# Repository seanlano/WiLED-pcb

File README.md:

# WiLED: PCB files

Circuit schematic and PCB for the WiLED main board, based on the ESP32 (ESP-WROOM-32) module. New version 3.0 of the board is an upgrade from the ESP8266-based version 1.0, but features improved layout and on-board LED driver components.

# Licence

All hardware schematics and design files are released under the CERN Open Hardware Licence v1.2. Please see [LICENCE](LICENCE) for details.

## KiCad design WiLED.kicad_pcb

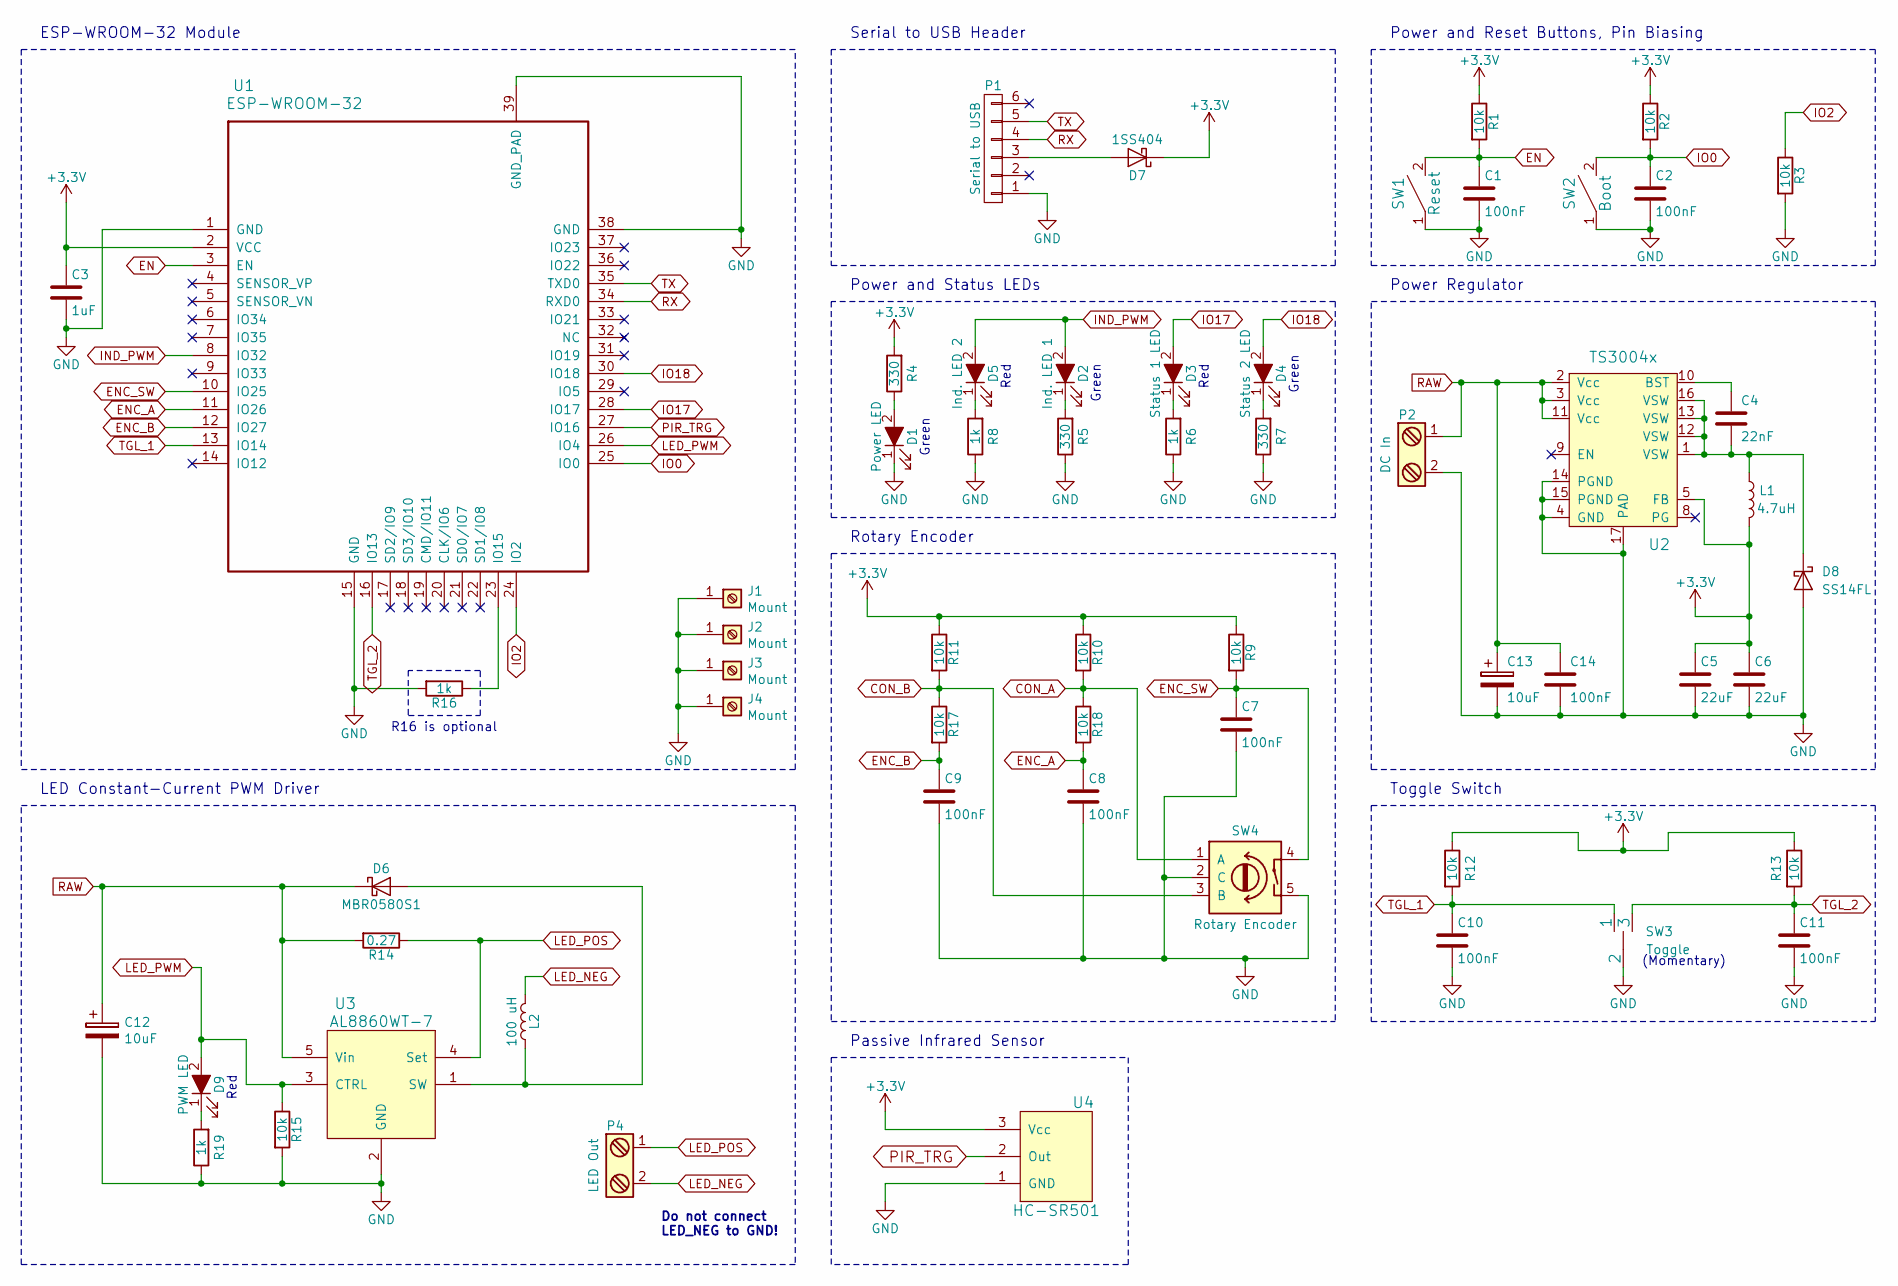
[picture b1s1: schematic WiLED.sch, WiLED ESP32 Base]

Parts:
C1, C2, C7, C8, C9, C10, C11, C14: 100nF; C_0805_2012Metric
C3: 1uF; C_0805_2012Metric
C4: 22nF; C_0805_2012Metric
C5, C6: 22uF; C_1206_3216Metric
C12, C13: 10uF
D1: Power LED; WL-SMCW
D2: Ind. LED 1; LED_D3.0mm
D3: Status 1 LED; WL-SMCW
D4: Status 2 LED; WL-SMCW
D5: Ind. LED 2; WL-SMCW
D6: MBR0580S1; D_SOD-123F
D7: 1SS404; D_SOD-323
D8: SS14FL; D_SOD-123F
D9: PWM LED; WL-SMCW
J1, J2, J3, J4: Mount; MountingHole_3.2mm_M3_ISO14580_Pad
L1: 4.7uH; L_Taiyo-Yuden_NR-40xx
L2: 100 uH; THT_Inductor_5mm
P1: Serial to USB; Pin_Header_Straight_1x06_Pitch2.54mm
P2: DC In; TerminalBlock_MetzConnect_Type059_RT06302HBWC_1x02_P3.50mm_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
P4: LED Out; TerminalBlock_MetzConnect_Type059_RT06302HBWC_1x02_P3.50mm_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
R1, R2, R3, R9, R10, R11, R12, R13, R15, R17, R18: 10k; R_0603_1608Metric
R4, R5, R7: 330; R_0603_1608Metric
R6, R8, R19: 1k; R_0603_1608Metric
R14: 0.27; R_0603_1608Metric_Pad1.05x0.95mm_HandSolder
R16: 1k; R_0603_1608Metric_Pad1.05x0.95mm_HandSolder
SW1: Reset; Button_6.5mm
SW2: Boot; Button_6.5mm
SW3: Toggle; Pin_Header_Straight_1x03_Pitch2.00mm
SW4: Rotary Encoder; PEC11R_5
U1: ESP-WROOM-32; ESP32-WROOM
U2: TS3004x; QFN-16-1EP_3x3mm_P0.5mm_EP2.7x2.7mm_ThermalVias
U3: AL8860WT-7; SOT-23-5
U4: HC-SR501; Pin_Header_Straight_1x03_Pitch2.00mm

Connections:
+3V3: C3.1, C5.1, C6.1, D7.1 (K), L1.2, R1.1, R2.1, R4.2, R9.1, R10.1, R11.1, R12.1, R13.1, U1.2 (VCC), U2.5 (FB), U4.3 (Vcc)
CON_A: R10.2, R18.1, SW4.1 (A)
CON_B: R11.2, R17.1, SW4.3 (B)
EN: C1.1, R1.2, SW1.2, U1.3 (EN)
ENC_A: C8.1, R18.2, U1.11 (IO26)
ENC_B: C9.1, R17.2, U1.12 (IO27)
ENC_SW: C7.1, R9.2, SW4.4, U1.10 (IO25)
GND: C1.2, C2.2, C3.2, C5.2, C6.2, C7.2, C8.2, C9.2, C10.2, C11.2, C12.2, C13.2, C14.2, D1.1 (K), D8.2 (A), J1.1, J2.1, J3.1, J4.1, P1.1, P2.2, R3.2, R5.1, R6.1, R7.1, R8.1, R15.2, R16.2, R19.1, SW1.1, SW2.1, SW3.2, SW4.2 (C), SW4.5, U1.1 (GND), U1.15 (GND), U1.38 (GND), U1.39 (GND_PAD), U2.4 (GND), U2.14 (PGND), U2.15 (PGND), U2.17 (PAD), U3.2 (GND), U4.1 (GND)
IND_PWM: D2.2 (A), D5.2 (A), U1.8 (IO32)
IO0: C2.1, R2.2, SW2.2, U1.25 (IO0)
IO2: R3.1, U1.24 (IO2)
IO17: D3.2 (A), U1.28 (IO17)
IO18: D4.2 (A), U1.30 (IO18)
LED_NEG: L2.2, P4.2
LED_POS: P4.1, R14.1, U3.4 (Set)
LED_PWM: D9.2 (A), R15.1, U1.26 (IO4), U3.3 (CTRL)
unnamed: C4.1, U2.10 (BST)
unnamed: C4.2, D8.1 (K), L1.1, U2.1 (VSW), U2.12 (VSW), U2.13 (VSW), U2.16 (VSW)
unnamed: D1.2 (A), R4.1
unnamed: D2.1 (K), R5.2
unnamed: D3.1 (K), R6.2
unnamed: D4.1 (K), R7.2
unnamed: D5.1 (K), R8.2
unnamed: D6.2 (A), L2.1, U3.1 (SW)
unnamed: D7.2 (A), P1.3
unnamed: D9.1 (K), R19.2
unnamed: R16.1, U1.23 (IO15)
PIR_TRG: U1.27 (IO16), U4.2 (Out)
RAW: C12.1, C13.1, C14.1, D6.1 (K), P2.1, R14.2, U2.2 (Vcc), U2.3 (Vcc), U2.11 (Vcc), U3.5 (Vin)
RX: P1.4, U1.34 (RXD0)
TGL_1: C10.1, R12.2, SW3.1, U1.13 (IO14)
TGL_2: C11.1, R13.2, SW3.3, U1.16 (IO13)
TX: P1.5, U1.35 (TXD0)

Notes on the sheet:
Power Regulator
Rotary Encoder
Serial to USB Header
Power and Status LEDs
Green
Power and Reset Buttons, Pin Biasing
ESP-WROOM-32 Module
Red
LED Constant-Current PWM Driver
Toggle Switch
(Momentary)
Do not connect LED_NEG to GND!
R16 is optional
Passive Infrared Sensor

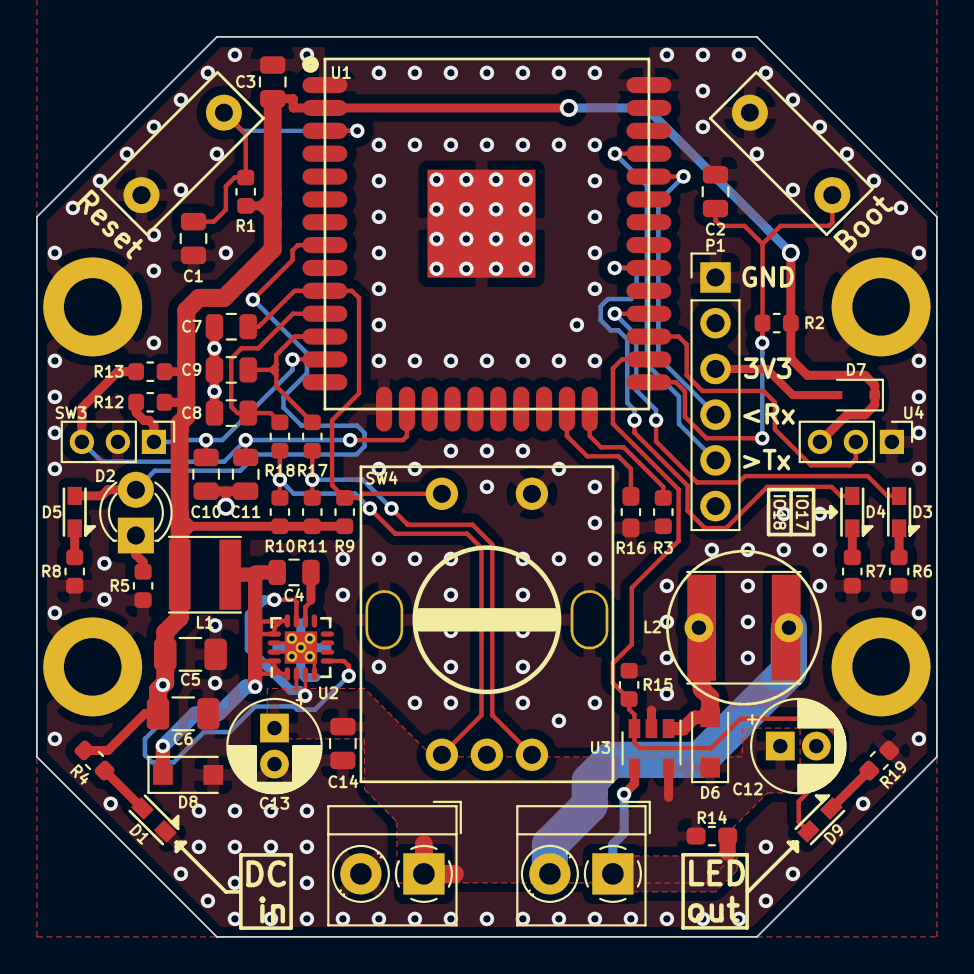
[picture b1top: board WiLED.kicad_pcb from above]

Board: 2 copper layers, 50.0 x 50.0 mm, 59 parts (0 on the bottom side), 33 nets.

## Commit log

2017-09-07 Initial git commit
2017-09-07 Add licence and README
2017-09-10 Removed auto-reset circuit
2017-09-10 Final draft
2017-09-10 First PCB traces
2017-09-11 Change LED_PWM and IND_PWM for better routing
2017-09-11 Further PCB routing
2017-09-11 First PCB draft
2017-09-12 Finalised first draft of PCB
2017-09-12 Second draft of PCB
2017-09-13 Update board edge and drill sizes
2017-09-18 Remove EN from DIO1 pin on Feather header
2017-09-18 Add SVG image of schematic
2017-09-18 Make SVG background white
2017-09-18 Add image to README
2017-09-18 Fix button labels on PCB
2017-09-18 Update PCB for plotting to Gerber
2017-09-25 Add pull-down on LED_PWM. Closes #1
2018-06-22 Update schematic to Version 2.0, using the ESP-WROOM-32
2018-07-01 First draft of v2.0 schematic and PCB
    This is the first complete schematic and PCB layout for version 2.0 of
    the WiLED main board. Some tweaks may be needed, but the general concept
    is complete.
2018-07-01 Add ground copper pours
2018-07-02 Increase via size and mounting hole size
    Vias were 0.4/0.6 mm, this has been increased to 0.4/0.8 mm to make
    manufacturing a little easier - and there's no reason to need the
    smaller size.
    The mounting holes were M2.5 size, but changed this to M3 for slightly
    more standard screw fittings.
2018-07-02 Rework LED constant-current PCB layout
    Previously there were unnecssarily long traces between high-power
    components in the buck-mode LED driver, this commit brings a modified
    layout that tries to improve on this.
2018-07-03 Tidy up board outline and improve ground planes
    Revised the board outline to make it a nice metric multiple.
    Also rerouted some traces to give a more contiguous ground plane.
2018-07-04 Add stitching vias to PCB
    The PCB now has numerous stitching vias for the ground planes.
    Also made some of the silk screen text slightly larger.
2018-07-08 Add PIR sensor and more stitching vias
    Added a connection for a HC-SR501 PIR sensor, to a spare GPIO on the
    ESP-32.
    Also increased the number of stitching vias.
2018-07-08 Add OSHW logo to silkscreen
2018-07-09 Add input voltage to silkscreen
2018-08-05 Correct pin mappings from unusable ESP32 pins
    Some LED indicators were assigned to ESP32 pins which are only available
    for input, and the toggle switch was mapped to the MTDO pin. Both of
    these mistakes are corrected in this commit.
2018-08-22 Update PCB for KiCad 5, and begin rerouting for new PSU
2018-08-22 Update schematic SVG
2018-08-22 Initial complete routing of PCB for v2.1
2018-09-01 Completed PCB routing
    Routing is complete, although there is quite some wasted space on the
    board - so a re-think is in order to further shrink the size of the
    board.
2018-09-01 Re-designed layout, with less wasted space
    Routing is completed, but vias still need to be added. The newer layout
    is much more space efficient.
2018-09-02 Add ground planes
2018-09-02 Add further stitching vias, layout mostly complete
2018-09-12 Move lower section components down slightly
    There is still a little bit more tightening that can be done vertically
    on the PCB layout. Some of the components on the lower part of the board
    have been moved down, to make space to move other components into.
    The PCB width is acceptable, but reducing the height would be ideal.
2018-09-14 Move top components down, shorten board height
2018-09-15 Re-do layout, for v3.0
    Having started the 3D CAD for the enclosure, it seems that the PCB is
    able to be slightly wider than previously planned. To make the most of
    this new width, a complete rearrange has been done - the PCB is now a
    square shape.
    Routing has been completed on this new layout, vias still need to be
    added.
2018-09-16 Add stiching vias
    Ground plane stitching vias have been added.
2018-09-23 Finalise v3.0 layout, add ESP32 3D model
    Layout is now complete for the v3.0 board, pending a review. Stitching
    vias are in place, and silkscreen has been updated.
    Also added a 3D model for the ESP32, to help with modelling the
    enclosure.
2018-09-24 Update URL on silkscreen
2018-09-25 Update 3D models for terminal block and encoder
    Found some manufacturer-supplied 3D models for the rotary encoder and
    the terminal block, so added these to the PCB.
2018-10-02 Change R14 to 0603 size
    R14 was originally an 0603 in v1.0, but was changed to an 0805 - looking
    at parts, 0603 are cheaper and still have the required values and
    tolerances, so 0603 should be used instead.
2018-10-08 Change C12 and C13 to through-hole electrolytic caps
    C12 and C13 were initially MLCCs, but these are harder to obtain and are
    more expensive than electrolytics - for this use case, the swap should
    be acceptable.
2018-10-09 Nudge C12 and C13 down slightly
    Moved C12 and C13 down, to make slightly more space for the screw when
    fitted into the mounting hole.
2018-10-10 Update model for pin headers, revise ground vias
    Updated the footprint for the 6-pin header P1, to one with a 3D model.
    Revised some ground plane vias, and re-routed some tracks to give
    slightly more contiguous ground plane regions.
2018-10-17 Change terminal blocks to 3.5 mm type
    The previous terminal blocks were the 5.08 mm type, which are quite
    large - larger than is needed. The 3.5 mm type should be enough, so
    changed the footprints and re-routed where needed.
2018-10-20 Update 3D models for screw terminal and rotary encoder
2018-10-20 Update README with PCB images
2018-10-29 Minor PCB tweaks
    As suggested by Oliver, made the following tweaks:
    - Added a keepout on the ground pour around L1
    - Made the small trace for the LED terminal block larger
    - Added a few arrows and a couple of labels for the LEDs
2018-10-30 Update drill hole sizes
    Rationalise a few drill hole sizes, to make manufacturing slightly
    easier.
